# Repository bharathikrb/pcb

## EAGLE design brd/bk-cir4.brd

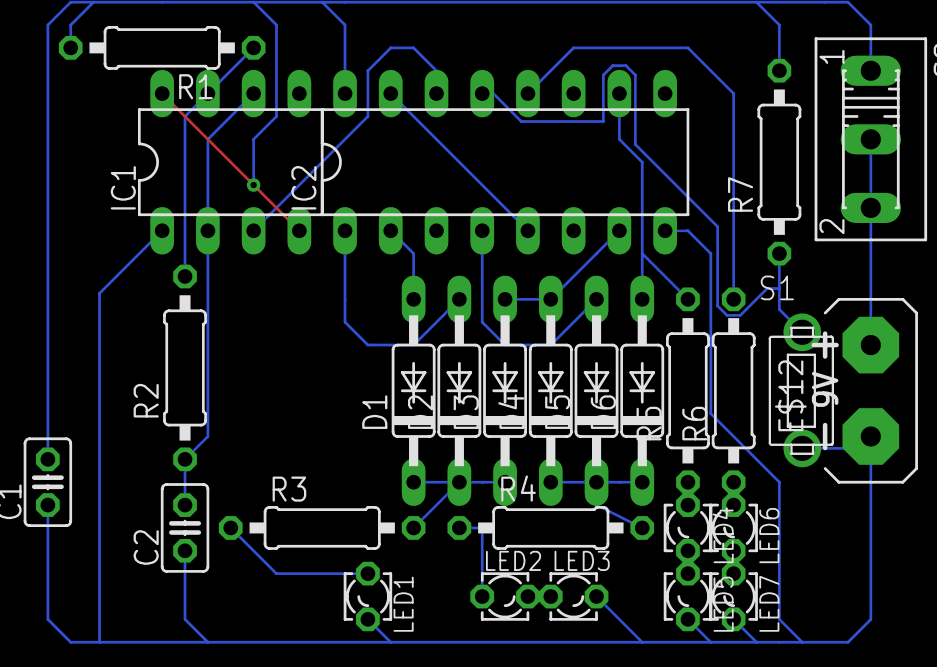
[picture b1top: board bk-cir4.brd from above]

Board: 2 copper layers, 27 parts (0 on the bottom side), 23 nets.

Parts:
C1: 0.1uF; C025-025X050
C2: 0.01uF; C025-025X050
D1, D2, D3, D4, D5, D6: C2992
E$12: AB9V
IC1: DIL08
IC2: DIL16
LED1, LED2, LED3, LED4, LED5, LED6, LED7: LZR181
R1: 1Ok; 0207/10
R2, R7: 10k; 0207/10
R3: 470; 0207/10
R4, R5, R6: 330; 0207/10
S1: FSM
S2: 255SB

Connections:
S$1: IC2.12, R6.2
S$2: IC2.5, IC2.15
S$3: D1.A, IC2.2
S$4: D2.A, IC2.1
S$5: D3.A, D4.A, IC2.7
S$6: D5.A, IC2.4
S$7: D6.A, IC2.10, R5.2
S$8: D1.C, D2.C, D3.C, R3.2
S$9: D4.C, D5.C, D6.C, R4.2
S$10: LED4.K, LED5.A
S$11: LED6.K, LED7.A
S$12: LED2.K, LED3.A
S$13: LED2.A, R4.1
S$14: LED1.A, R3.1
S$15: LED4.A, R5.1
S$16: LED6.A, R6.1
S$17: IC2.13, R7.1, S1.P$1
S$18: C2.2, IC1.2, IC1.6, R2.1
S$19: IC1.7, R1.1, R2.2
S$20: IC1.3, IC2.14
S$21: E$12.+, S2.2, S2.3
S$23: C1.1, C2.1, E$12.-, IC1.1, IC2.8, LED1.K, LED3.K, LED5.K, LED7.K, S1.P$2
S$25: C1.2, IC1.4, IC1.8, IC2.16, R1.2, R7.2, S2.1

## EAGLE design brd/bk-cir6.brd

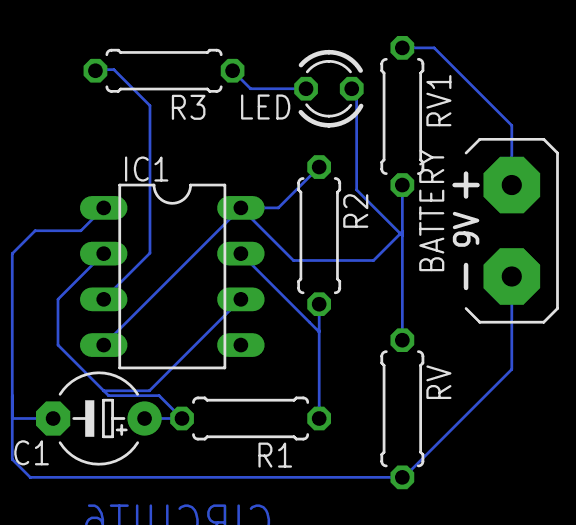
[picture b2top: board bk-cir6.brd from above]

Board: 2 copper layers, 9 parts (0 on the bottom side), 7 nets.

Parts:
BATTERY: AB9V
C1: E5-5
IC1: DIL08
LED: LED3MM
R1, R2, R3: 0207/7
RV, RV1: 4k; 0207/7

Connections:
S$1: IC1.7, R1.1, R2.2
S$2: IC1.3, R3.2
S$4: LED.K, R3.1
S$5: BATTERY.+, RV1.1
S$6: BATTERY.-, C1.-, IC1.1, RV.2
S$7: C1.+, IC1.2, IC1.6, R1.2
S$9: IC1.4, IC1.8, LED.A, R2.1, RV.1, RV1.2

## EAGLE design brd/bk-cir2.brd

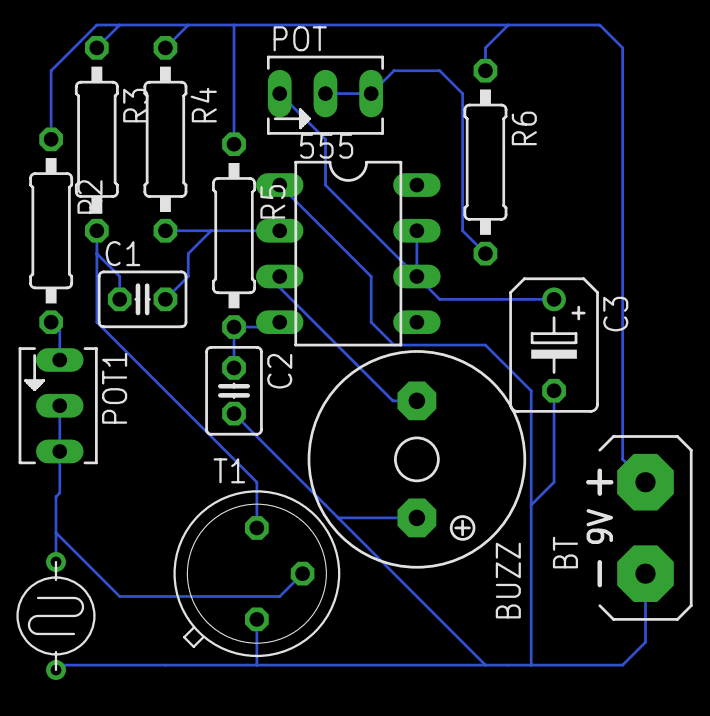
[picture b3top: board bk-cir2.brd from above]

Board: 2 copper layers, 15 parts (0 on the bottom side), 10 nets.

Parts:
555: DIL08
BT: AB9V
BUZZ: F/QMBIII
C1: 0.1uF; C025-030X050
C2: 0.01uF; C025-030X050
C3: 10uF; B45181B
LDR: LDR-PG5
POT: 1M; B64Y
POT1: 100k; B64Y
R2: 10k; 0207/10
R3, R4, R5: 1M; 0207/10
R6: 47k; 0207/10
T1: TO5

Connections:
S$1: 555.1, BT.-, BUZZ.+, C2.2, C3.-, LDR.1, T1.1
S$3: 555.4, C2.1, R5.2
S$4: 555.3, BUZZ.-
S$5: 555.6, 555.7, C3.+, POT.E
S$6: LDR.2, POT1.A, POT1.S, T1.2
S$7: POT1.E, R2.2
S$8: 555.2, C1.2, R4.2
S$9: C1.1, R3.2, T1.3
S$11: POT.A, POT.S, R6.2
S$12: BT.+, R2.1, R3.1, R4.1, R5.1, R6.1

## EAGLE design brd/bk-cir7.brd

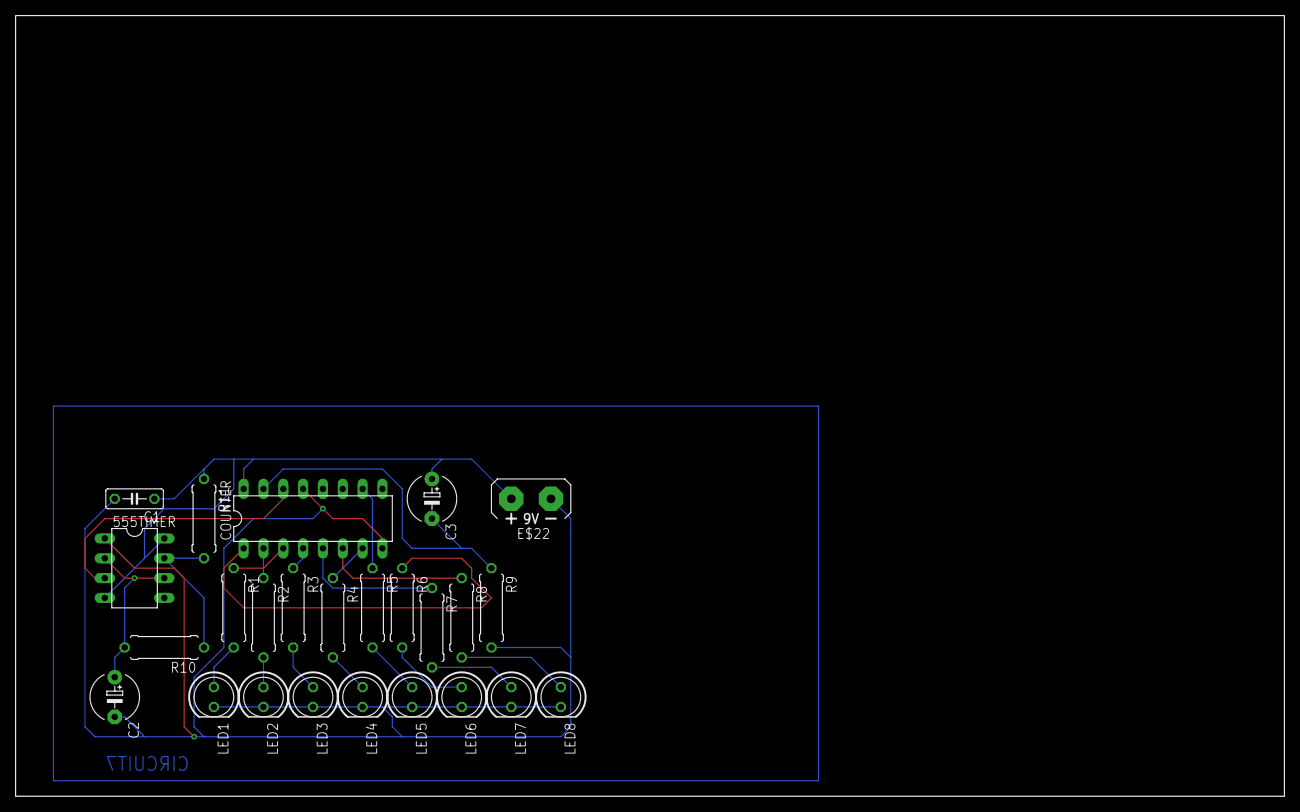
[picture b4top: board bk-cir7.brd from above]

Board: 2 copper layers, 162.5 x 100.0 mm, 25 parts (0 on the bottom side), 22 nets.

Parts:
555TIMER: DIL08
C1: C050-025X075
C2: .01uF; E5-6
C3: 1uF; E5-6
COUNTER: DIL16
E$22: AB9V
LED1, LED2, LED3, LED4, LED5, LED6, LED7, LED8: LED5MM
R1, R2, R3, R4, R5, R6, R7, R8: 560; 0309/10
R9: 22K; 0309/10
R10: 180K; 0309/10
R11: 2.2K; 0309/10

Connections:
S$1: COUNTER.3, R1.1
S$2: COUNTER.2, R2.1
S$3: COUNTER.4, R3.1
S$4: COUNTER.7, R4.1
S$5: COUNTER.10, R5.1
S$6: COUNTER.1, R6.1
S$7: COUNTER.5, R7.1
S$8: LED6.A, R6.2
S$9: 555TIMER.1, C1.2, C2.-, COUNTER.8, COUNTER.13, E$22.-, LED1.K, LED2.K, LED3.K, LED4.K, LED5.K, LED6.K, LED7.K, LED8.K, R9.2
S$11: 555TIMER.7, R10.1, R11.2
S$12: 555TIMER.2, 555TIMER.6, C2.+, R10.2
S$13: LED1.A, R1.2
S$14: LED2.A, R2.2
S$15: LED3.A, R3.2
S$16: LED4.A, R4.2
S$17: LED5.A, R5.2
S$19: LED7.A, R7.2
S$20: LED8.A, R8.2
S$21: COUNTER.6, R8.1
S$24: 555TIMER.3, COUNTER.14
S$25: C3.-, COUNTER.15, R9.1
S$26: 555TIMER.4, 555TIMER.8, C1.1, C3.+, COUNTER.16, E$22.+, R11.1

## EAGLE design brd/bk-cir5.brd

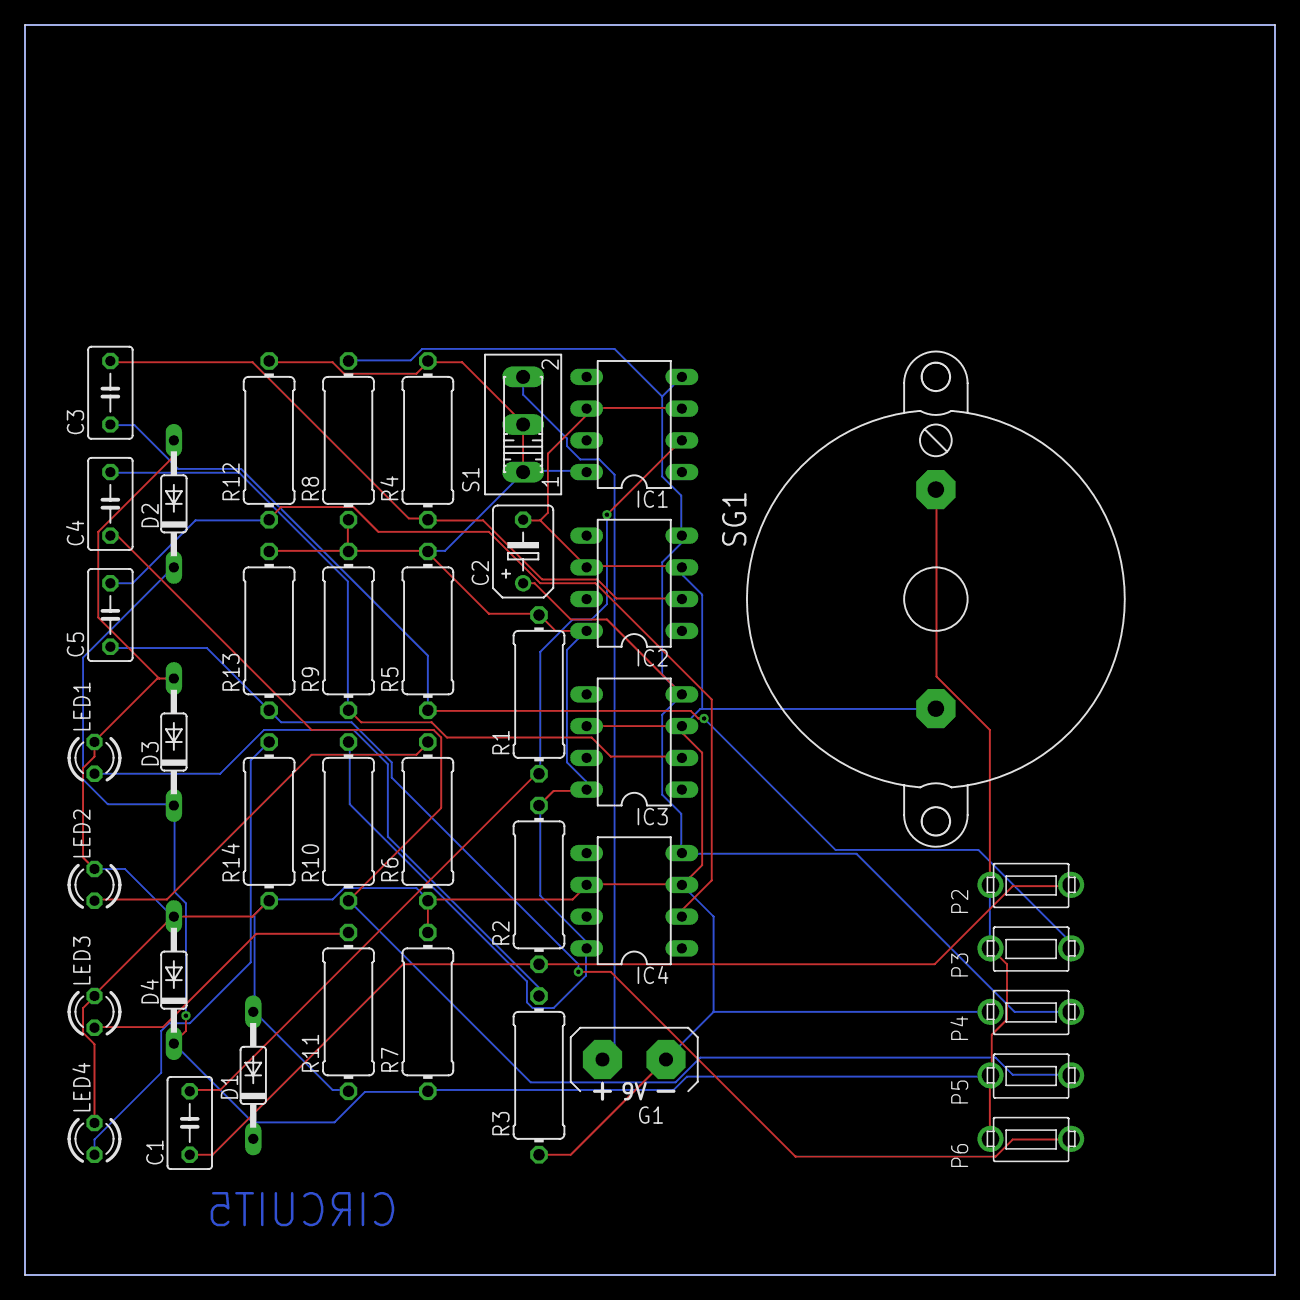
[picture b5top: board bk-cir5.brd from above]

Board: 2 copper layers, 100.0 x 100.0 mm, 39 parts (0 on the bottom side), 17 nets.

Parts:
C1, C3, C4, C5: 0.1uF; C050-035X075
C2: 1uF; B45181B
D1, D2, D3, D4: 1N4148DO35-10; DO35-10
G1: AB9V
IC1, IC2, IC3, IC4: DIL08
LED1, LED2, LED3, LED4: LED3MM
P2, P3, P4, P5, P6: FSM
R1, R2, R4, R5, R9, R10, R12, R13: 10k; 0411/12
R3, R6, R11, R14: 470; 0411/12
R7, R8: 1k; 0411/12
S1: 255SB
SG1: F/BC35

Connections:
unnamed: C1.2, IC1.2, R1.1
unnamed: LED1.A, R3.2
unnamed: C1.1, P2.P$2, R2.1
unnamed: IC1.8, IC2.8, IC3.8, IC4.8, R1.2, R2.2, R4.2, R5.2, R8.1, R9.2, R10.2, R12.2, R13.2, S1.1, S1.2
unnamed: G1.+, S1.3
unnamed: C3.2, IC2.2, R4.1
unnamed: LED2.A, R6.2
unnamed: C3.1, P3.P$2, R5.1
unnamed: C2.+, IC1.4, IC2.4, IC3.4, IC4.4, P4.P$2, R8.2
unnamed: C2.-, D1.A, D2.A, D3.A, D4.A, G1.-, IC1.3, IC1.6, IC2.3, IC2.6, IC3.3, IC3.6, IC4.3, IC4.6, LED1.K, LED2.K, LED3.K, LED4.K, P4.P$1, R3.1, R6.1, R7.2, R11.1, R14.1, SG1.-
unnamed: C4.2, IC3.2, R9.1
unnamed: C4.1, P5.P$2, R10.1
unnamed: LED3.A, R11.2
unnamed: C5.2, IC4.2, R12.1
unnamed: C5.1, P6.P$2, R13.1
unnamed: LED4.A, R14.2
unnamed: D1.C, D2.C, D3.C, D4.C, P2.P$1, P3.P$1, P5.P$1, P6.P$1, R7.1, SG1.+

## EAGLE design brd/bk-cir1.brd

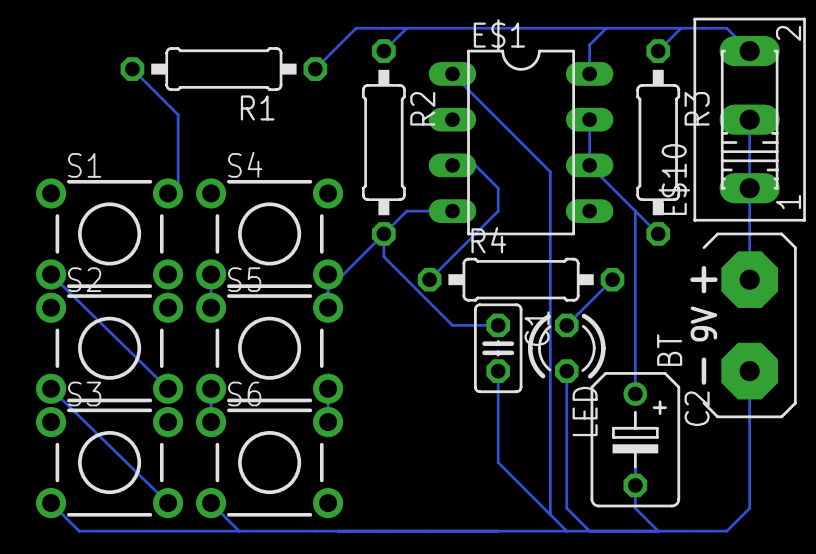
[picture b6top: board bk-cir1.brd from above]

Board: 2 copper layers, 16 parts (0 on the bottom side), 12 nets.

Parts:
BT: AB9V
C1: 0.1uF; C025-025X050
C2: 1uF; B45181B
E$1: DIL08
E$10: 255SB
LED: LED3MM
R1, R2: 100k; 0207/10
R3: 1M; 0207/10
R4: 470; 0207/10
S1, S2, S3, S4, S5, S6: TL1105

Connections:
S$2: E$1.3, R4.1
S$3: C2.+, E$1.6, E$1.7, R3.2
S$4: BT.+, E$10.1, E$10.2
S$5: E$1.8, E$10.3, R1.1, R2.1, R3.1
S$6: LED.A, R4.2
S$7: BT.-, C1.2, C2.-, E$1.1, LED.K, S3.4, S6.4
S$8: C1.1, E$1.4, R2.2, S4.2, S5.1
S$9: S1.4, S2.2
S$10: S5.2, S6.1
S$11: S4.4, S5.3
S$12: S5.4, S6.3
S$13: S2.4, S3.2

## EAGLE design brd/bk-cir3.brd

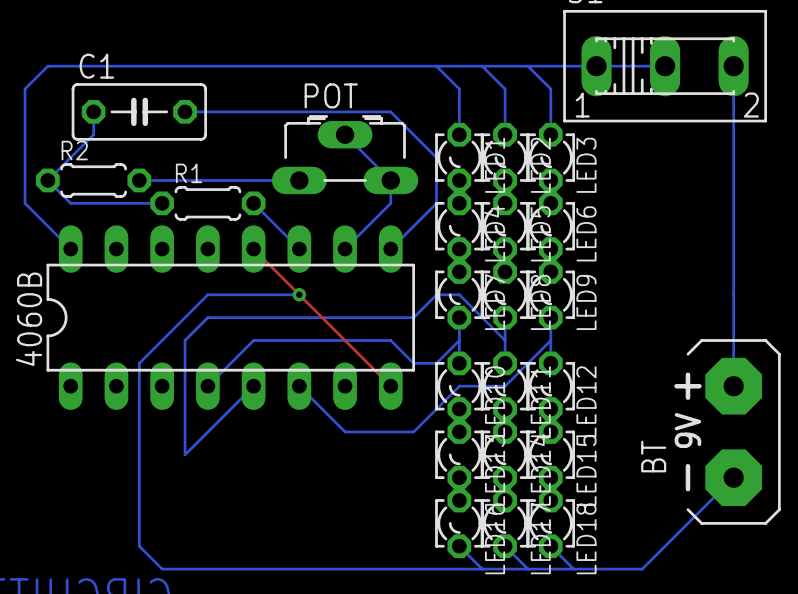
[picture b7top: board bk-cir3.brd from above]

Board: 2 copper layers, 25 parts (0 on the bottom side), 23 nets.

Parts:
4060B: DIL16
BT: AB9V
C1: 0.1uF; C050-030X075
LED1, LED2, LED3, LED4, LED5, LED6, LED7, LED8, LED9, LED10, LED11, LED12, LED13, LED14, LED15, LED16, LED17, LED18: LZR181
POT: 47k; CA6H
R1: 470k; 0204/5
R2: 10k; 0204/5
S1: 255SB

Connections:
S$1: POT.A, R2.2
S$2: 4060B.10, POT.E, POT.S
S$3: 4060B.9, C1.2
S$4: C1.1, R1.1, R2.1
S$5: LED1.K, LED4.A
S$6: LED4.K, LED7.A
S$7: LED2.K, LED5.A
S$8: LED5.K, LED8.A
S$9: LED6.K, LED9.A
S$10: LED3.K, LED6.A
S$11: LED10.K, LED13.A
S$12: LED13.K, LED16.A
S$13: LED14.K, LED17.A
S$14: LED11.K, LED14.A
S$15: LED12.K, LED15.A
S$16: LED15.K, LED18.A
S$18: 4060B.11, R1.2
S$19: 4060B.8, 4060B.12, BT.-, LED16.K, LED17.K, LED18.K
S$20: 4060B.16, LED1.A, LED2.A, LED3.A, S1.1, S1.2
S$21: 4060B.5, LED8.K, LED11.A
S$23: BT.+, S1.3
S$26: 4060B.6, LED9.K, LED12.A
S$28: 4060B.4, LED7.K, LED10.A
